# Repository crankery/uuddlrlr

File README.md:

# uuddlrlr

Uuddlrlr is just another joystick module for Eurorack.

This is a though hole implementation of the [CCTV Ouija](https://www.cctv.fm/product-page/ouija-eurorack-diy-kit) module. I had pretty much all the parts for this laying around (including the Chinese copy of the Omter joystick) so I decided to just lay it out and fool around with it.

This is not done. Please don't build it. If you're really smart and you see that I've done something really stuipd, I'd be pleased to hear from you. I am, after all, just copying somebody else's work here while I watch stupid stuff on YouTube.

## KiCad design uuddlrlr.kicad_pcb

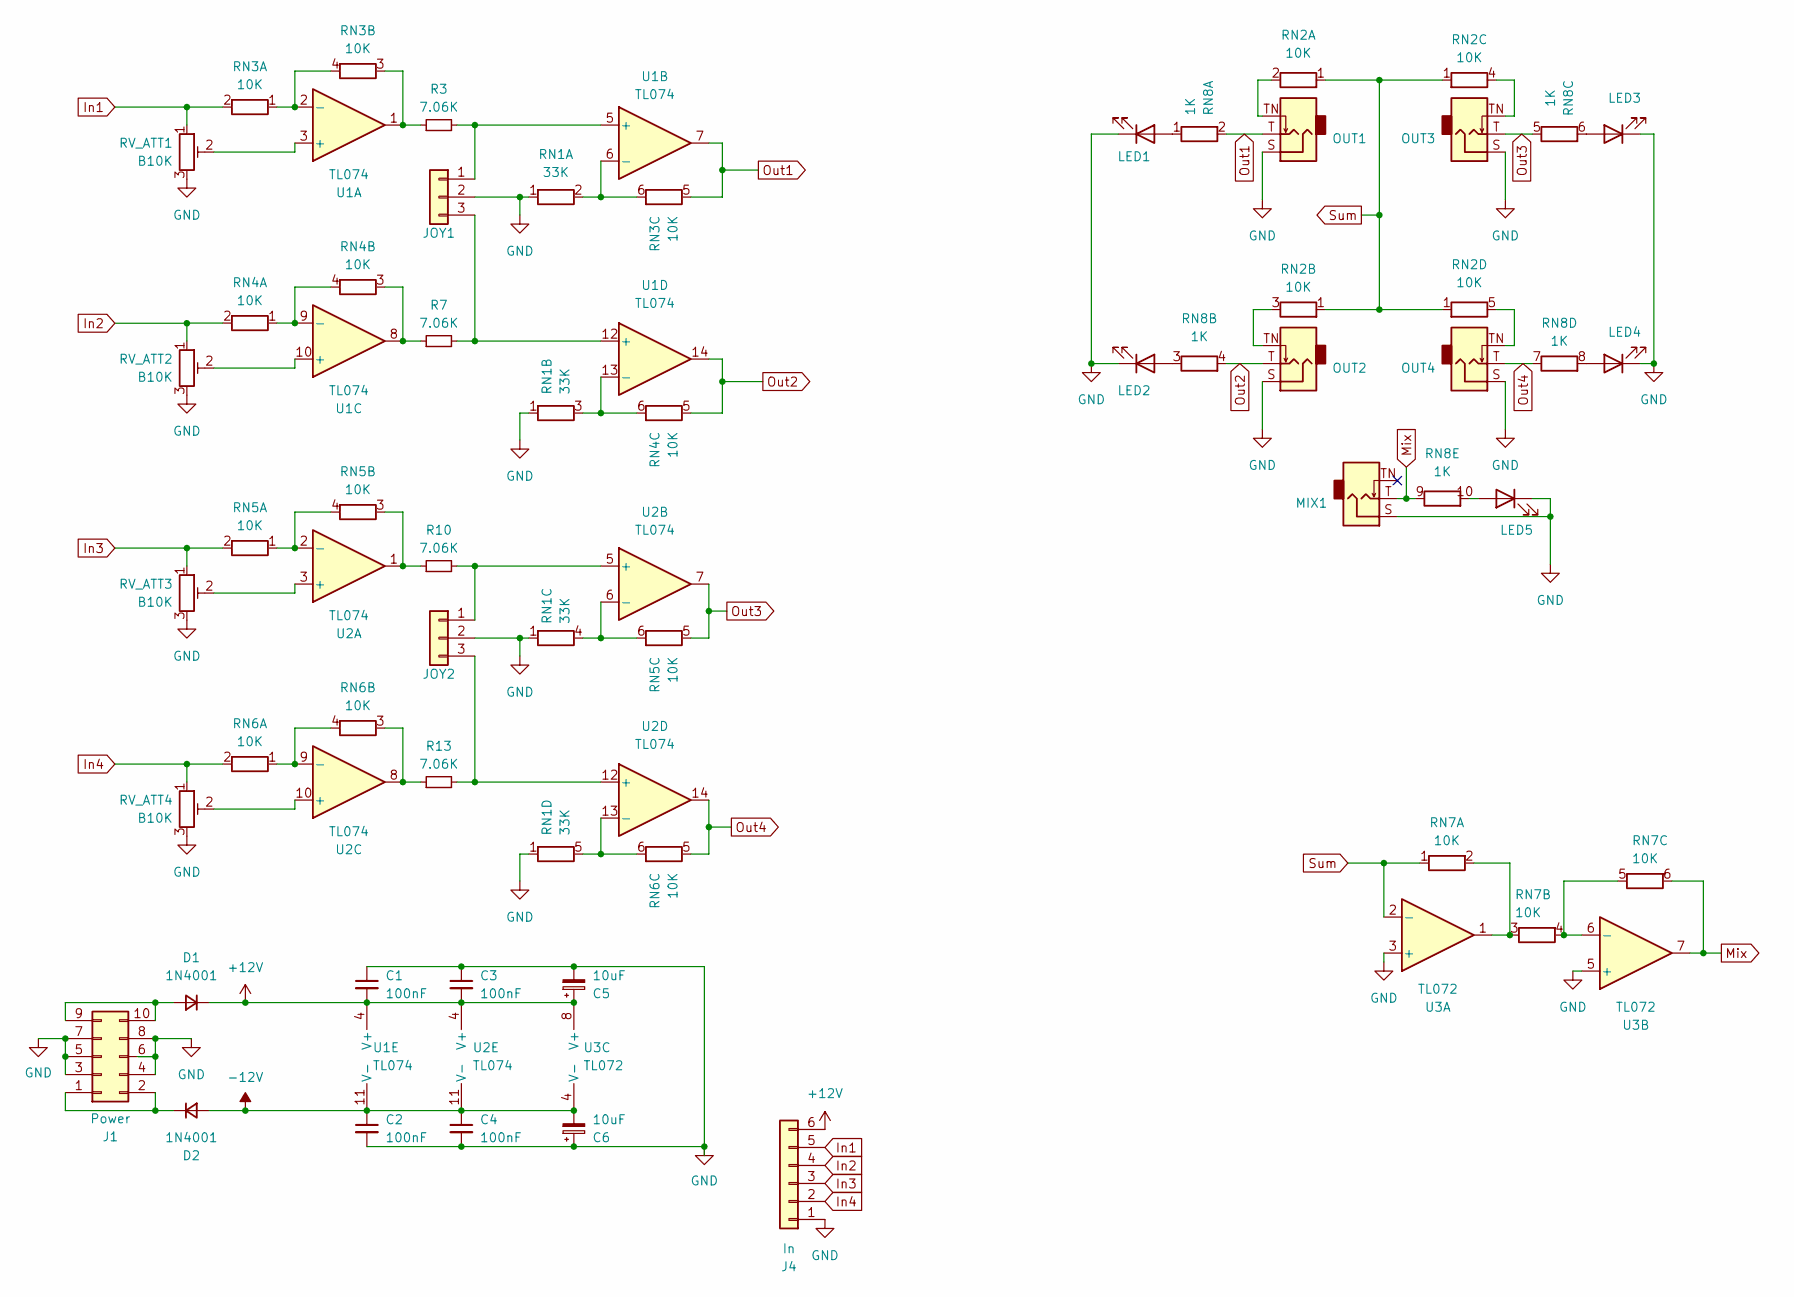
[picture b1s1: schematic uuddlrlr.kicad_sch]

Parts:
C1, C2, C3, C4: 100nF; C_Disc_D3.0mm_W2.0mm_P2.50mm
C5, C6: 10uF; CP_Radial_D5.0mm_P2.50mm
D1, D2: 1N4001; D_DO-41_SOD81_P7.62mm_Horizontal
J1: Power; PinHeader_2x05_P2.54mm_Vertical
J4: In; PinHeader_1x06_P2.54mm_Vertical
JOY1: JOY1; PinHeader_1x03_P2.54mm_Vertical
JOY2: JOY2; PinHeader_1x03_P2.54mm_Vertical
LED1, LED2, LED3, LED4, LED5: LED; LED_D3.0mm
MIX1: MIX; Jack_3.5mm_QingPu_WQP-PJ301BM_Vertical
OUT1: OUT1; Jack_3.5mm_QingPu_WQP-PJ301BM_Vertical
OUT2: OUT2; Jack_3.5mm_QingPu_WQP-PJ301BM_Vertical
OUT3: OUT3; Jack_3.5mm_QingPu_WQP-PJ301BM_Vertical
OUT4: OUT4; Jack_3.5mm_QingPu_WQP-PJ301BM_Vertical
R3, R7, R10, R13: 7.06K; R_Axial_DIN0204_L3.6mm_D1.6mm_P5.08mm_Horizontal
RN1: 33K; R_Array_SIP5
RN2: 10K; R_Array_SIP5
RN3, RN4, RN5, RN6, RN7: 10K; R_Array_SIP6
RN8: 1K; R_Array_SIP10
RV_ATT1, RV_ATT2, RV_ATT3, RV_ATT4: B10K; Alpha_RD901F_Single_Vertical
U1, U2: TL074; DIP-14_W7.62mm
U3: TL072; DIP-8_W7.62mm

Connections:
+12V: C1.2, C3.2, C5.1, D1.1 (K), J4.6, U1.4 (V+), U2.4 (V+), U3.8 (V+)
-12V: C2.1, C4.1, C6.2, D2.2 (A), U1.11 (V-), U2.11 (V-), U3.4 (V-)
GND: C1.1, C2.2, C3.1, C4.2, C5.2, C6.1, J1.3, J1.4, J1.5, J1.6, J1.7, J1.8, J4.1, JOY1.2, JOY2.2, LED1.1 (K), LED2.1 (K), LED3.1 (K), LED4.1 (K), LED5.1 (K), MIX1.S, OUT1.S, OUT2.S, OUT3.S, OUT4.S, RN1.1 (R1), RV_ATT1.3, RV_ATT2.3, RV_ATT3.3, RV_ATT4.3, U3.3 (+), U3.5 (+)
In1: J4.5, RN3.2 (R1.2), RV_ATT1.1
In2: J4.4, RN4.2 (R1.2), RV_ATT2.1
In3: J4.3, RN5.2 (R1.2), RV_ATT3.1
In4: J4.2, RN6.2 (R1.2), RV_ATT4.1
Mix: MIX1.T, RN7.6 (R3.2), RN8.9 (R5.1), U3.7
unnamed: D1.2 (A), J1.9, J1.10
unnamed: D2.1 (K), J1.1, J1.2
unnamed: JOY1.1, R3.2, U1.5 (+)
unnamed: JOY1.3, R7.2, U1.12 (+)
unnamed: JOY2.1, R10.2, U2.5 (+)
unnamed: JOY2.3, R13.2, U2.12 (+)
unnamed: LED1.2 (A), RN8.1 (R1.1)
unnamed: LED2.2 (A), RN8.3 (R2.1)
unnamed: LED3.2 (A), RN8.6 (R3.2)
unnamed: LED4.2 (A), RN8.8 (R4.2)
unnamed: LED5.2 (A), RN8.10 (R5.2)
unnamed: RN1.2 (R1.2), RN3.6 (R3.2), U1.6 (-)
unnamed: RN1.3 (R2.2), RN4.6 (R3.2), U1.13 (-)
unnamed: RN1.4 (R3.2), RN5.6 (R3.2), U2.6 (-)
unnamed: RN1.5 (R4.2), RN6.6 (R3.2), U2.13 (-)
unnamed: OUT1.TN, RN2.2 (R1.2)
unnamed: OUT2.TN, RN2.3 (R2.2)
unnamed: OUT3.TN, RN2.4 (R3.2)
unnamed: OUT4.TN, RN2.5 (R4.2)
unnamed: RN3.1 (R1.1), RN3.4 (R2.2), U1.2 (-)
unnamed: R3.1, RN3.3 (R2.1), U1.1
unnamed: RN4.1 (R1.1), RN4.4 (R2.2), U1.9 (-)
unnamed: R7.1, RN4.3 (R2.1), U1.8
unnamed: RN5.1 (R1.1), RN5.4 (R2.2), U2.2 (-)
unnamed: R10.1, RN5.3 (R2.1), U2.1
unnamed: RN6.1 (R1.1), RN6.4 (R2.2), U2.9 (-)
unnamed: R13.1, RN6.3 (R2.1), U2.8
unnamed: RN7.2 (R1.2), RN7.3 (R2.1), U3.1
unnamed: RN7.4 (R2.2), RN7.5 (R3.1), U3.6 (-)
unnamed: RV_ATT1.2, U1.3 (+)
unnamed: RV_ATT2.2, U1.10 (+)
unnamed: RV_ATT3.2, U2.3 (+)
unnamed: RV_ATT4.2, U2.10 (+)
Out1: OUT1.T, RN3.5 (R3.1), RN8.2 (R1.2), U1.7
Out2: OUT2.T, RN4.5 (R3.1), RN8.4 (R2.2), U1.14
Out3: OUT3.T, RN5.5 (R3.1), RN8.5 (R3.1), U2.7
Out4: OUT4.T, RN6.5 (R3.1), RN8.7 (R4.1), U2.14
Sum: RN2.1 (R1), RN7.1 (R1.1), U3.2 (-)

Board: 2 copper layers, 41 parts (27 on the bottom side), 46 nets, no tracks yet.

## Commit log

2023-07-23 ignore mac stuff
2023-07-23 about to start drawing wires
2023-07-23 add joystick drawings
